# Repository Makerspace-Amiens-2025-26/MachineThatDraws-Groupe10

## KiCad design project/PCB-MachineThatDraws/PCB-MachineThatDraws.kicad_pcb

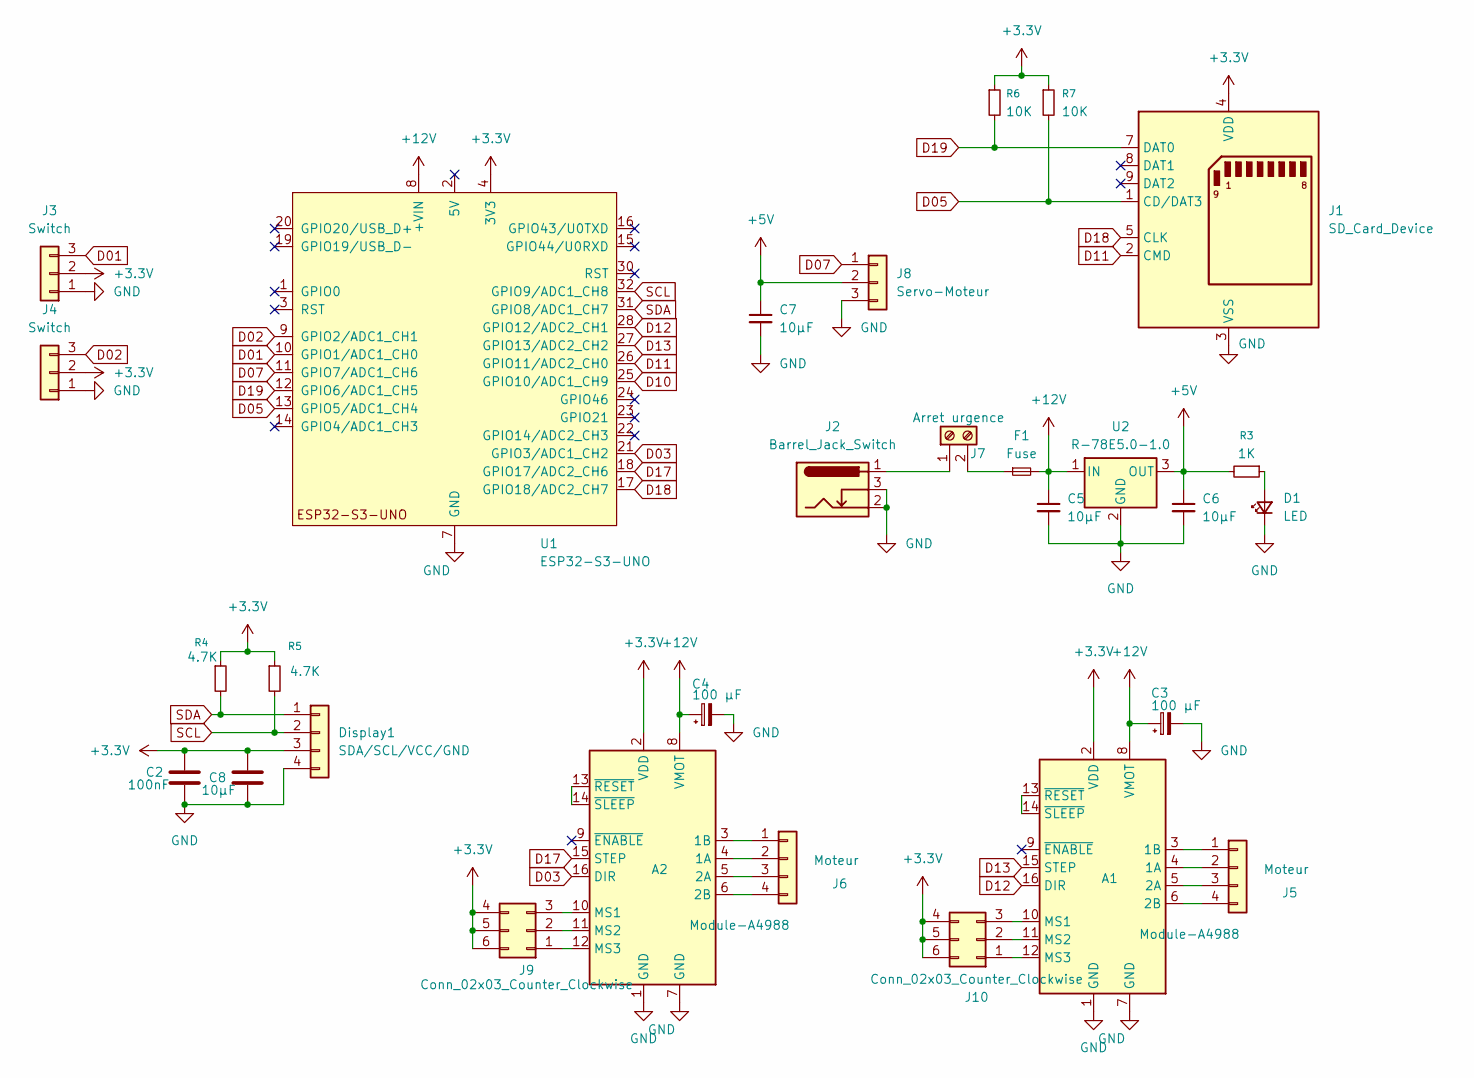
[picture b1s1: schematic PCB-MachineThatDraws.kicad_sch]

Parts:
A1, A2: Module-A4988; Pololu_Breakout-16_15.2x20.3mm
C2: 100nF; C_1206
C3, C4: 100 µF; CP_Elec_6.3x5.4
C5, C6, C7, C8: 10µF; C_1206
D1: LED; LED_1206_3216Metric
Display1: SDA/SCL/VCC/GND; PinHeader_1x04_P2.54mm_Vertical
F1: Fuse; Fuseholder_Blade_Mini_Keystone_3568
J1: SD_Card_Device; SD_Hirose_DM1AA_SF_PEJ82
J2: Barrel_Jack_Switch; BarrelJack_GCT_DCJ200-10-A_Horizontal
J3, J4: Switch; PinHeader_1x03_P2.54mm_Vertical
J5, J6: Moteur; PinHeader_1x04_P2.54mm_Vertical
J7: Arret urgence; TerminalBlock_bornier-2_P5.08mm
J8: Servo-Moteur; PinHeader_1x03_P2.54mm_Vertical
J9, J10: Conn_02x03_Counter_Clockwise; PinHeader_2x03_P2.54mm_Vertical
R3: 1K; R_1206
R4, R5: 4.7K; R_1206
R6, R7: 10K; R_1206
U1: ESP32-S3-UNO; ESP_S3_UNO
U2: R-78E5.0-1.0; Converter_DCDC_RECOM_R-78E-0.5_THT

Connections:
+3.3V: A1.2 (VDD), A2.2 (VDD), C2.1, C8.1, Display1.3, J1.4 (VDD), J3.2, J4.2, J9.4, J9.5, J9.6, J10.4, J10.5, J10.6, R4.1, R5.1, R6.1, R7.1, U1.4 (3V3)
+5V: C6.1, C7.1, J8.2, R3.2, U2.3 (OUT)
+12V: A1.8 (VMOT), A2.8 (VMOT), C3.1, C4.1, C5.1, F1.2, U1.8 (+VIN), U2.1 (IN)
D01: J3.3, U1.10 (GPIO1/ADC1_CH0)
D02: J4.3, U1.9 (GPIO2/ADC1_CH1)
D03: A2.16 (DIR), U1.21 (GPIO3/ADC1_CH2)
D05: J1.1 (CD/DAT3), R7.2, U1.13 (GPIO5/ADC1_CH4)
D07: J8.1, U1.11 (GPIO7/ADC1_CH6)
D10: U1.25 (GPIO10/ADC1_CH9)
D11: J1.2 (CMD), U1.26 (GPIO11/ADC2_CH0)
D12: A1.16 (DIR), U1.28 (GPIO12/ADC2_CH1)
D13: A1.15 (STEP), U1.27 (GPIO13/ADC2_CH2)
D17: A2.15 (STEP), U1.18 (GPIO17/ADC2_CH6)
D18: J1.5 (CLK), U1.17 (GPIO18/ADC2_CH7)
D19: J1.7 (DAT0), R6.2, U1.12 (GPIO6/ADC1_CH5)
GND: A1.1 (GND), A1.7 (GND), A2.1 (GND), A2.7 (GND), C2.2, C3.2, C4.2, C5.2, C6.2, C7.2, C8.2, D1.1 (K), Display1.4, J1.3 (VSS), J1.6 (VSS), J2.2, J2.3, J3.1, J4.1, J8.3, U1.6 (GND), U1.7 (GND), U1.29 (GND), U2.2 (GND)
unnamed: A1.4 (1A), J5.2
unnamed: A1.3 (1B), J5.1
unnamed: A1.5 (2A), J5.3
unnamed: A1.6 (2B), J5.4
unnamed: A1.10 (MS1), J10.3
unnamed: A1.11 (MS2), J10.2
unnamed: A1.12 (MS3), J10.1
unnamed: A1.13 (~RESET), A1.14 (~SLEEP)
unnamed: A2.4 (1A), J6.2
unnamed: A2.3 (1B), J6.1
unnamed: A2.5 (2A), J6.3
unnamed: A2.6 (2B), J6.4
unnamed: A2.10 (MS1), J9.3
unnamed: A2.11 (MS2), J9.2
unnamed: A2.12 (MS3), J9.1
unnamed: A2.13 (~RESET), A2.14 (~SLEEP)
unnamed: D1.2 (A), R3.1
unnamed: J2.1, J7.1
unnamed: F1.1, J7.2
SCL: U1.32 (GPIO9/ADC1_CH8)
SCL: Display1.2, R5.2
SDA: Display1.1, R4.2
SDA: U1.31 (GPIO8/ADC1_CH7)

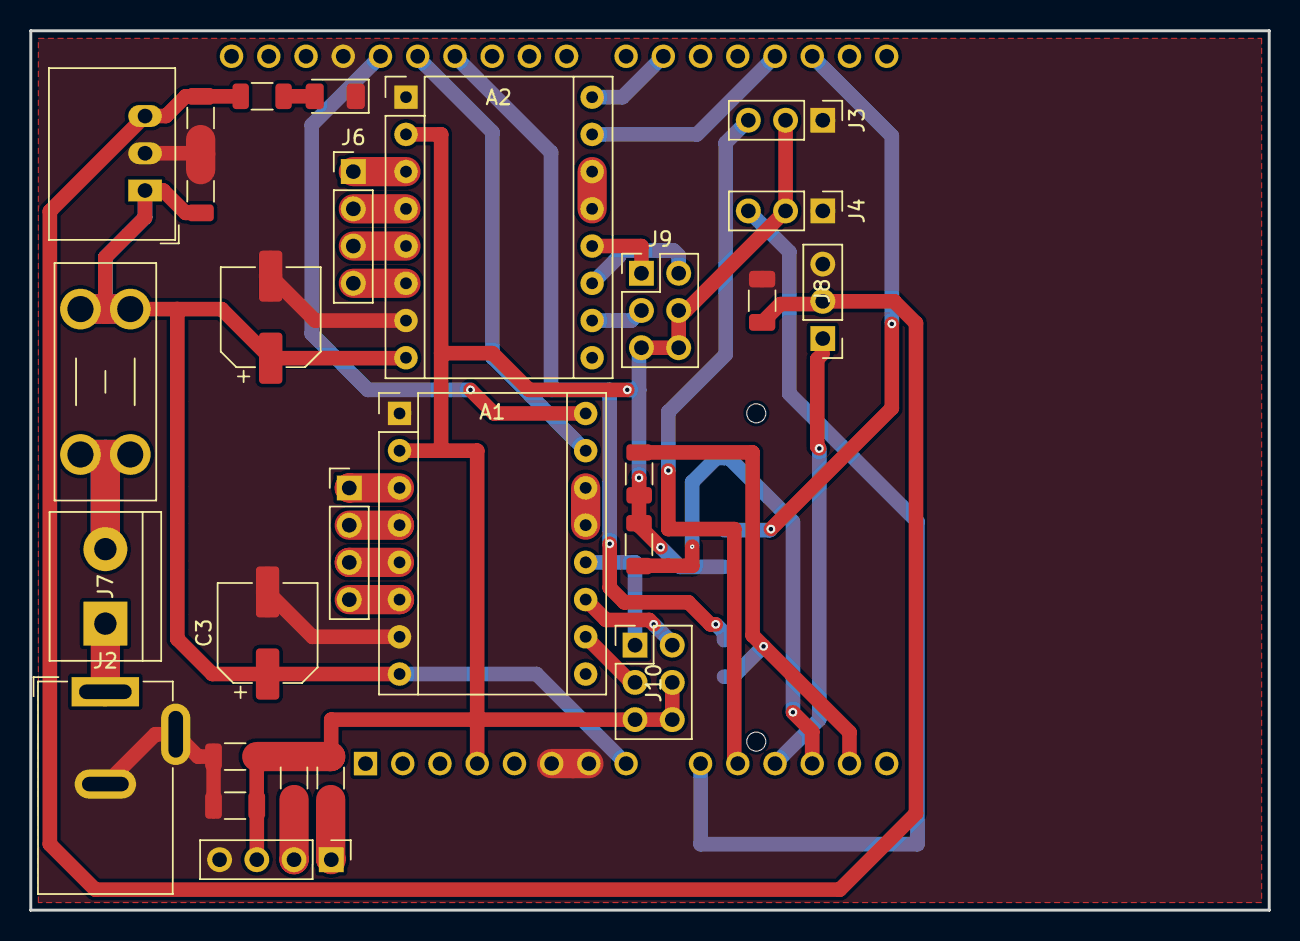
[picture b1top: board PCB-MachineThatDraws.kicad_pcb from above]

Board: 2 copper layers, 84.5 x 60.0 mm, 29 parts (1 on the bottom side), 36 nets.

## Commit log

2026-03-15 Create Fichier Kicad
    Fichier Kicad pour la carte électronique du projet Machine That Draws
2026-03-20 Create index.html
    Site de présentation de notyre projet
2026-03-20 Update index.md
    teste
2026-03-20 Update index.md
    test template
2026-03-20 Update index.md
    ajout du fond noir / police en blanc + ajout d'un rendu 3D
2026-03-20 Update index.md
    changement de couleur pouvoir avoir la marge en noir
2026-03-20 Change directory - update pcb
2026-03-20 update resistor pullup I2C
2026-03-25 changement nom / esp / valeur
2026-04-02 Kicad
2026-04-03 Update Gemfile
2026-04-03 Faire PCB
2026-04-04 A refaire
2026-04-05 A repenser
2026-04-05 Finale
2026-04-07 petites modifications apportées
2026-04-14 Peut etre a revoir
2026-04-22 A verifier
2026-04-24 Validation PCB pour production
2026-04-27 fix some wiring problems
2026-06-03 mise à jour du site
2026-06-03 ajout de style css
